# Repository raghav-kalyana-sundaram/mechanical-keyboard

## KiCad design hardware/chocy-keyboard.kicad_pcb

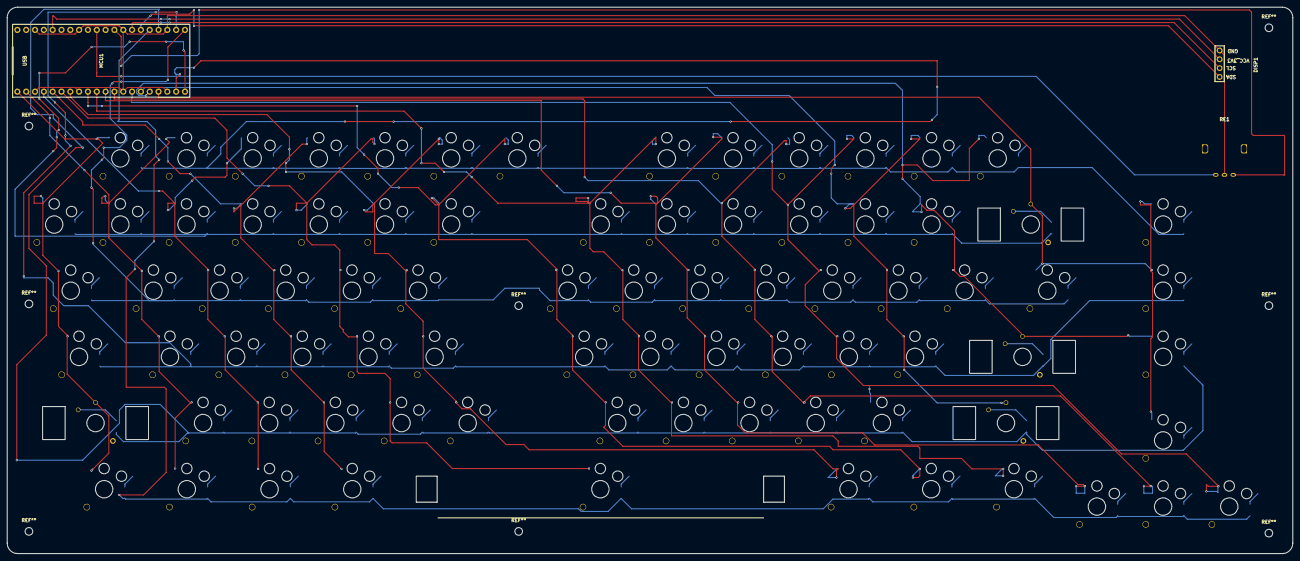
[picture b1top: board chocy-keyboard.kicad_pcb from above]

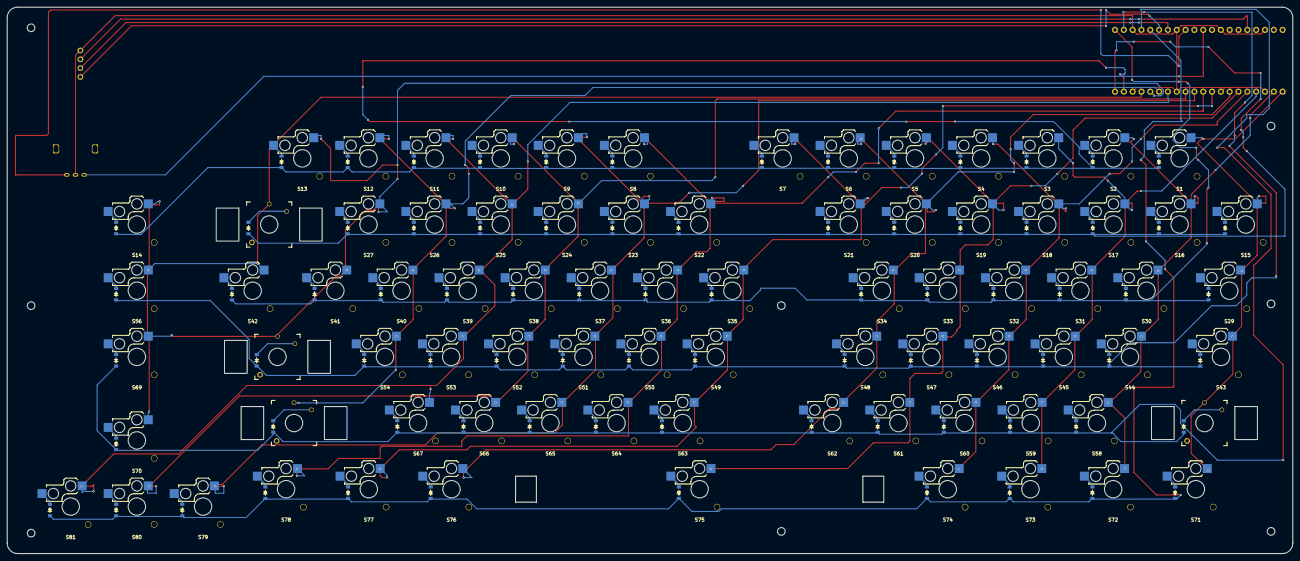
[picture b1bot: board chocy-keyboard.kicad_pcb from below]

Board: 2 copper layers, 370.1 x 157.3 mm, 166 parts (162 on the bottom side), 107 nets.

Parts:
D1, D2, D3, D4, D5, D6, D7, D8, D9, D10, D11, D12, D13, D14, D15, D16, D17, D18, D19, D20, D21, D22, D23, D24, D25, D26, D27, D28, D29, D30, D31, D32, D33, D34, D35, D36, D37, D38, D39, D40, D41, D42, D43, D44, D45, D46, D47, D48, D49, D50, D51, D52, D53, D54, D55, D56, D57, D58, D59, D60, D61, D62, D63, D64, D65, D66, D67, D68, D69, D70, D71, D72, D73, D74, D75, D76, D77, D78, D79, D80, D81: diode_tht_sod123
DISP1: display_ssd1306
MCU1: RaspberryPi_Pico_2x20
RE1: rotary_encoder_ec11_ec12
S1, S2, S3, S4, S5, S6, S7, S8, S9, S10, S11, S12, S13, S14, S15, S16, S17, S18, S19, S20, S21, S22, S23, S24, S25, S26, S27, S29, S30, S31, S32, S33, S34, S35, S36, S37, S38, S39, S40, S41, S42, S43, S44, S45, S46, S47, S48, S49, S50, S51, S52, S53, S54, S56, S58, S59, S60, S61, S62, S63, S64, S65, S66, S67, S69, S70, S71, S72, S73, S74, S75, S76, S77, S78, S79, S80, S81: switch_choc_v1_v2
S28, S55, S57, S68: SW_Kailh_Choc_V2_THT
SW2: KEY_SWITCH; Choc_v2_PCBMountStab_6.25u

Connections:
C0: MCU1.1, S1.1, S15.1, S29.1, S43.1, S57.1, S71.1
C1: MCU1.2, S2.1, S16.1, S30.1, S44.1, S58.1, S72.1
C2: MCU1.4, S3.1, S17.1, S31.1, S45.1, S59.1, S73.1
C3: MCU1.5, S4.1, S18.1, S32.1, S46.1, S60.1, S74.1
C4: MCU1.6, S5.1, S19.1, S33.1, S47.1, S61.1, S75.1
C5: MCU1.7, S6.1, S20.1, S34.1, S48.1, S62.1, S76.1
C6: MCU1.9, S7.1, S21.1, S35.1, S49.1, S63.1, S77.1
C7: MCU1.10, S8.1, S22.1, S36.1, S50.1, S64.1, S78.1
C8: MCU1.11, S9.1, S23.1, S37.1, S51.1, S65.1, S79.1
C9: MCU1.12, S10.1, S24.1, S38.1, S52.1, S66.1, S80.1
C10: MCU1.14, S11.1, S25.1, S39.1, S53.1, S67.1, S81.1
C11: MCU1.15, S12.1, S26.1, S40.1, S54.1, S68.1
C12: MCU1.16, S13.1, S27.1, S41.1, S55.1, S69.1
C13: MCU1.17, S14.1, S28.1, S42.1, S56.1, S70.1
ENC_A: MCU1.29, RE1.A
ENC_B: MCU1.31, RE1.C
GND: DISP1.4, MCU1.3, MCU1.8, MCU1.13, MCU1.18, MCU1.23, MCU1.28, MCU1.33, MCU1.38, RE1.B
K_0: D25.2, S25.2
K_1: D16.2, S16.2
K_2: D17.2, S17.2
K_3: D18.2, S18.2
K_4: D19.2, S19.2
K_5: D20.2, S20.2
K_6: D21.2, S21.2
K_7: D22.2, S22.2
K_8: D23.2, S23.2
K_9: D24.2, S24.2
K_A: D44.2, S44.2
K_B: D62.2, S62.2
K_BACKSLASH: D42.2, S42.2
K_BACKSPACE: D28.2, S28.2
K_C: D60.2, S60.2
K_CAPS: D43.2, S43.2
K_COMMA: D65.2, S65.2
K_D: D46.2, S46.2
K_DELETE: D14.2, S14.2
K_DOT: D66.2, S66.2
K_DOWN: D80.2, S80.2
K_E: D32.2, S32.2
K_ENTER: D55.2, S55.2
K_EQUAL: D27.2, S27.2
K_ESC: D1.2, S1.2
K_F: D47.2, S47.2
K_F1: D2.2, S2.2
K_F2: D3.2, S3.2
K_F3: D4.2, S4.2
K_F4: D5.2, S5.2
K_F5: D6.2, S6.2
K_F6: D7.2, S7.2
K_F7: D8.2, S8.2
K_F8: D9.2, S9.2
K_F9: D10.2, S10.2
K_F10: D11.2, S11.2
K_F11: D12.2, S12.2
K_F12: D13.2, S13.2
K_FN: D71.2, S71.2
K_G: D48.2, S48.2
K_GRAVE: D15.2, S15.2
K_H: D49.2, S49.2
K_I: D37.2, S37.2
K_J: D50.2, S50.2
K_K: D51.2, S51.2
K_L: D52.2, S52.2
K_LBRACKET: D40.2, S40.2
K_LCMD: D74.2, S74.2
K_LCTRL: D72.2, S72.2
K_LEFT: D79.2, S79.2
K_LOPT: D73.2, S73.2
K_LSHIFT: D57.2, S57.2
K_M: D64.2, S64.2
K_MINUS: D26.2, S26.2
K_N: D63.2, S63.2
K_O: D38.2, S38.2
K_P: D39.2, S39.2
K_PGDN: D69.2, S69.2
K_PGUP: D56.2, S56.2
K_Q: D30.2, S30.2
K_QUOTE: D54.2, S54.2
K_R: D33.2, S33.2
K_RBRACKET: D41.2, S41.2
K_RCMD: D76.2, S76.2
K_RCTRL: D78.2, S78.2
K_RIGHT: D81.2, S81.2
K_ROPT: D77.2, S77.2
K_RSHIFT: D68.2, S68.2
K_S: D45.2, S45.2
K_SEMICOLON: D53.2, S53.2
K_SLASH: D67.2, S67.2
K_SPACE: D75.2, S75.2
K_T: D34.2, S34.2
K_TAB: D29.2, S29.2
K_U: D36.2, S36.2
K_UP: D70.2, S70.2
K_V: D61.2, S61.2
K_W: D31.2, S31.2
K_X: D59.2, S59.2
K_Y: D35.2, S35.2
K_Z: D58.2, S58.2
R0: D1.1, D2.1, D3.1, D4.1, D5.1, D6.1, D7.1, D8.1, D9.1, D10.1, D11.1, D12.1, D13.1, D14.1, MCU1.19
R1: D15.1, D16.1, D17.1, D18.1, D19.1, D20.1, D21.1, D22.1, D23.1, D24.1, D25.1, D26.1, D27.1, D28.1, MCU1.20
R2: D29.1, D30.1, D31.1, D32.1, D33.1, D34.1, D35.1, D36.1, D37.1, D38.1, D39.1, D40.1, D41.1, D42.1, MCU1.21
R3: D43.1, D44.1, D45.1, D46.1, D47.1, D48.1, D49.1, D50.1, D51.1, D52.1, D53.1, D54.1, D55.1, D56.1, MCU1.22
R4: D57.1, D58.1, D59.1, D60.1, D61.1, D62.1, D63.1, D64.1, D65.1, D66.1, D67.1, D68.1, D69.1, D70.1, MCU1.24
R5: D71.1, D72.1, D73.1, D74.1, D75.1, D76.1, D77.1, D78.1, D79.1, D80.1, D81.1, MCU1.25
SCL: DISP1.2, MCU1.27
SDA: DISP1.1, MCU1.26
VCC_3V3: DISP1.3, MCU1.36
